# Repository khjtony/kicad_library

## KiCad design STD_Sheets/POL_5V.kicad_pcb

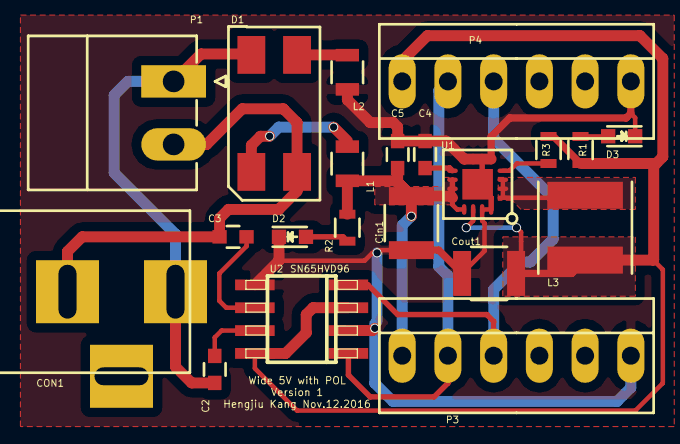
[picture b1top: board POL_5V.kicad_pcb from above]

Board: 2 copper layers, 21 parts (0 on the bottom side), 16 nets.

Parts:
C2, C3: 10uF; C_0603
C4: 3.3nF; C_0603
C5: 0.1uF; C_0603
CON1: BARREL_JACK
Cin1: 10uF; C_1210
Cout1: 22uF; C_1210
D1: Diode_Bridge; SOIC-4
D2, D3: LED; LED_0603
L1, L2: 10uH; R_0805
L3: 2.2uH; Inductor_Taiyo-Yuden_MD-5050
P1: CONN_01X02; PhoenixContact_MC-G_02x3.50mm_Angled
P3, P4: CONN_01X06; PINHEAD1-6
R1: 100K; R_0603
R2: 10k; R_0603
R3: 4.7K; R_0603
U1: tps62153A; VQFN_16
U2: SN65HVD96; KLibrary-SOIC8

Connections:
/D: P3.3, P4.3, U2.4
/R: P3.2, P4.2, U2.1
/V5V: Cout1.1, L3.2, P4.1, R1.1, R3.1, U1.14, U2.3, U2.8
/V+: C2.1, CON1.1, D1.4, P1.1
/V-: C3.1, CON1.2, D1.2, P1.2
/V_RAW: C5.1, Cin1.1, L1.2, P3.1, R2.1, U1.10, U1.11, U1.12, U1.13
GND: C4.1, C5.2, Cin1.2, Cout1.2, D2.1, D3.1, L2.1, P3.6, P4.6, U1.5, U1.6, U1.7, U1.8, U1.15, U1.16, U1.17, U2.2, U2.5
unnamed: C2.2, U2.7
unnamed: C3.2, U2.6
unnamed: C4.2, U1.9
unnamed: D1.1, L1.1
unnamed: D1.3, L2.2
unnamed: D2.2, R2.2
unnamed: D3.2, R3.2
unnamed: L3.1, U1.1, U1.2, U1.3
unnamed: R1.2, U1.4

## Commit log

2017-10-09 init commit
